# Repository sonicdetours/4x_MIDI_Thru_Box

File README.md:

DIY 4x MIDI Thru Box with LED
=============================

This project contains schematic, PCB layout and Bill of Materials for a very simple DIY 4 x MIDI Thru box with Activity LED.

See https://sonicdetours.com/2014/06/22/4-x-midi-thru-box-simple-diy-project/

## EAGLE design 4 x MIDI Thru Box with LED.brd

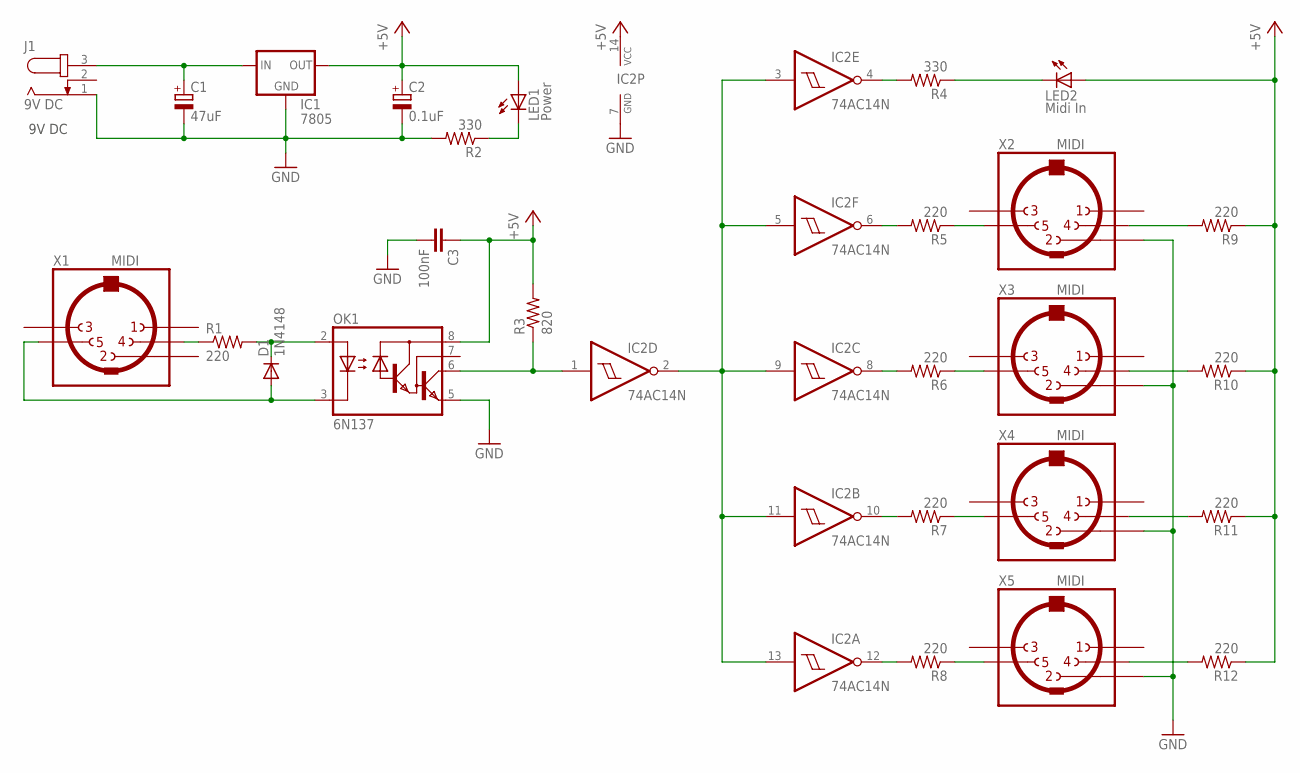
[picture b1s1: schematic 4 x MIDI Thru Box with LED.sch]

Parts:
C1: 47uF; TT2D6
C2: 0.1uF; TT2D6
C3: 100nF; C025-024X044
D1: 1N4148; D-5
IC1: 7805; 78XXS
IC2: 74AC14N; DIL14
J1: 9V DC; SPC4078_BIG_HOLES
LED1: Power; LED3MM
LED2: Midi In; LED3MM
OK1: 6N137; DIL08
R1, R5, R6, R7, R8, R9, R10, R11, R12: 220; 0204/7
R2, R4: 330; 0204/7
R3: 820; 0204/7
X1, X2, X3, X4, X5: MIDI; MAB5SH

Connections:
+5V: C2.+, C3.1, IC1.OUT, IC2.14 (VCC), LED1.A, LED2.A, OK1.8 (VCC), R3.2, R9.1, R10.1, R11.1, R12.1
GND: C1.-, C2.-, C3.2, IC1.GND, IC2.7 (GND), J1.1, OK1.5 (GND), R2.2, X2.2, X3.2, X4.2, X5.2
MIDI_IN: IC2.1 (I), OK1.6 (VO), R3.1
unnamed: IC2.6 (O), R5.2
unnamed: IC2.10 (O), R7.2
unnamed: R8.1, X5.5
unnamed: R9.2, X2.4
unnamed: LED2.K (C), R4.1
unnamed: C1.+, IC1.IN, J1.3
unnamed: R1.1, X1.4
unnamed: LED1.K (C), R2.1
unnamed: D1.A, OK1.3 (C), X1.5
unnamed: D1.C, OK1.2 (A), R1.2
unnamed: IC2.2 (O), IC2.3 (I), IC2.5 (I), IC2.9 (I), IC2.11 (I), IC2.13 (I)
unnamed: R7.1, X4.5
unnamed: IC2.8 (O), R6.2
unnamed: R5.1, X2.5
unnamed: IC2.12 (O), R8.2
unnamed: R6.1, X3.5
unnamed: R12.2, X5.4
unnamed: R11.2, X4.4
unnamed: R10.2, X3.4
unnamed: IC2.4 (O), R4.2

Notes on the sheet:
9V DC

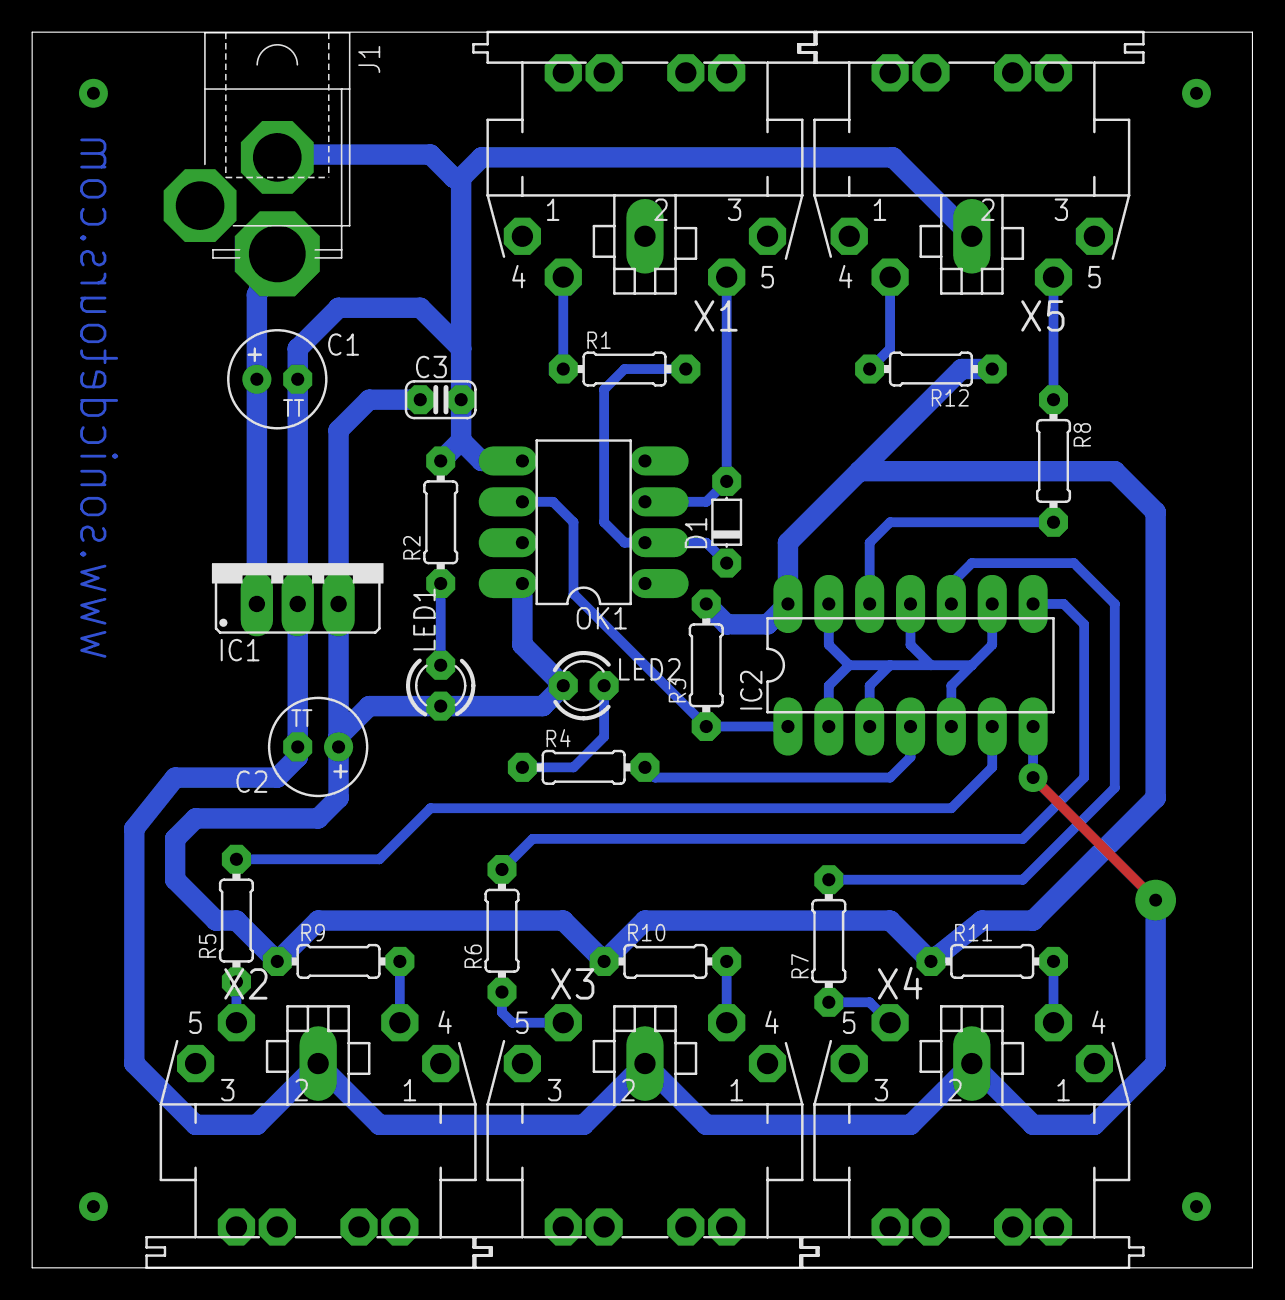
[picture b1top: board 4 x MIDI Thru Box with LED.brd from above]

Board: 2 copper layers, 75.9 x 76.8 mm, 27 parts (0 on the bottom side), 23 nets.

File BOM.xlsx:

Reference | Description | Package | Value | Quantity | www.el-supply.dk
J1 | DC Jack | 2.1 mm |  | 1 | 5207B
X1-X5 | DIN 180 Socket, 5P |  |  | 5 | 4912A
D1 | 1N4148 | DO-41 |  | 2 | 251N4148
IC1 | LM7805 | TO220 | +5V | 1 | 2827805
IC2 | 74AC14N | DIP14 |  | 1
OK1 | 6N137 | DIP8 |  | 1 | 3842
C1 | Electrolytic | 1.58 mm pitch | 47uF | 1 | 211D2471
C2 | Electrolytic | 2.54 mm pitch | 0.1uF | 1 | 211H0011
C3 | Ceramic | 2.54 mm pitch | 100nF | 1 | 1851100
R1, R4-R11 | Metal film resistor 1% |  | 220 | 9 | 63220
R2 | Metal film resistor 1% |  | 820 | 1 | 63820
R3 | Metal film resistor 1% |  | 330 | 1 | 63330
LED1 | White LED |  |  | 1
 | DIP8 Socket |  |  | 1 | 4751
 | DIP14Socket |  |  | 1 | 4752

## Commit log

2014-04-27 Added BOM
2014-05-25 Started PCB design
2014-05-31 Completed PCB design
2014-06-21 Version 1.0
2016-03-13 Updated PDF to latest design
